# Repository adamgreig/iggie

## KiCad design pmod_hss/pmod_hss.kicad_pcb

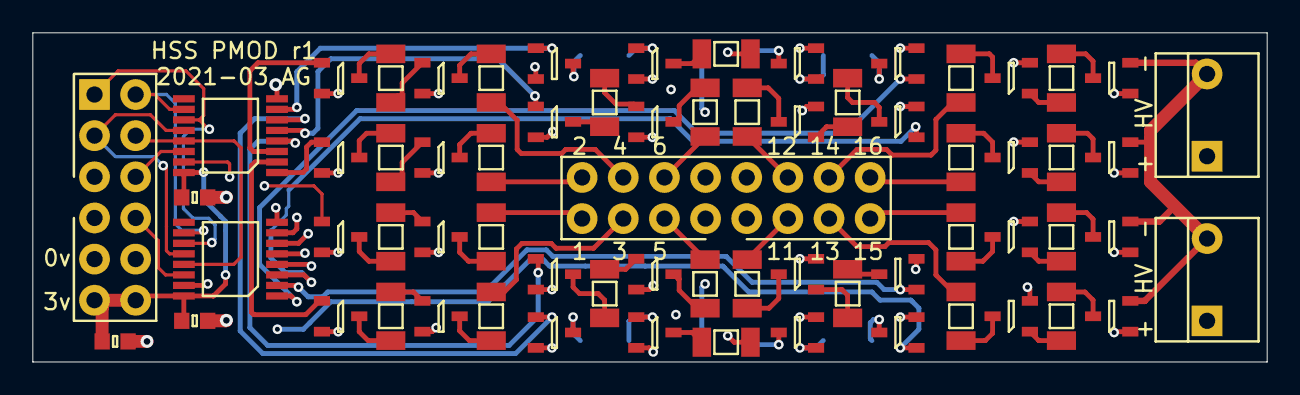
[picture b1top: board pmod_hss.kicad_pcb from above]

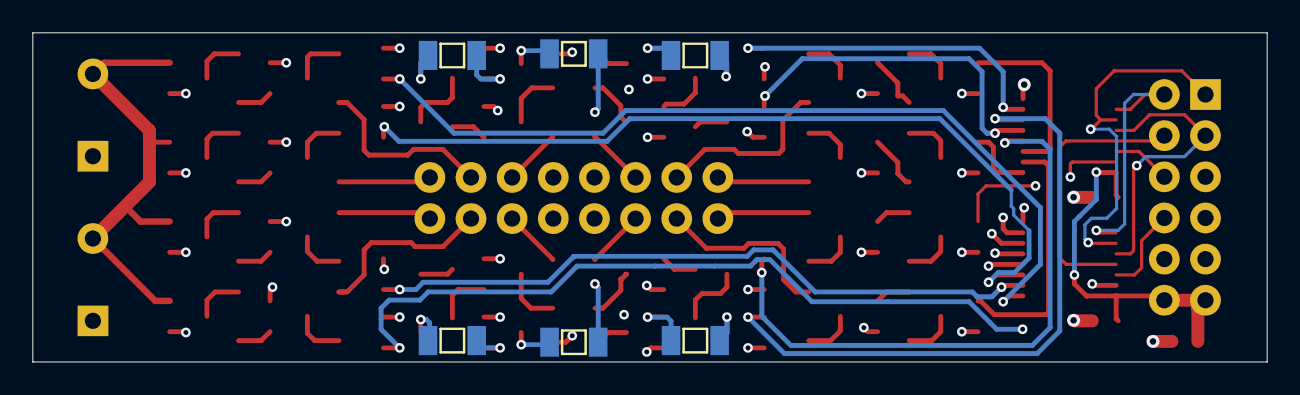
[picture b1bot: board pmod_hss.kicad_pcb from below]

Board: 4 copper layers, 76.2 x 20.3 mm, 73 parts (6 on the bottom side), 90 nets.

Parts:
C1, C2, C3: 100n; 0603
IC1, IC2: 74HC595; TSSOP-16
J1, J2: HV; MOLEX-KK-254P-03
J3: PMOD; DIL-254P-12
J4: ANODES; DIL-254P-16
Q1, Q3, Q5, Q7, Q9, Q11, Q13, Q15, Q17, Q19, Q21, Q23, Q25, Q27, Q29, Q31: PBHV9050T,215; SOT-23
Q2, Q4, Q6, Q8, Q10, Q12, Q14, Q16, Q18, Q20, Q22, Q24, Q26, Q28, Q30, Q32: DMN60H080DS-7; SOT-23
R1, R3, R5, R7, R9, R11, R13, R15, R17, R19, R21, R23, R25, R27, R29, R31: 1M; 1206
R2, R4, R6, R8, R10, R12, R14, R16, R18, R20, R22, R24, R26, R28, R30, R32: 93k1; 1206

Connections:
3v3: C1.2, C2.1, C3.2, IC1.16 (VCC), IC2.16 (VCC), J3.11, J3.12
/AN1: J4.1, R2.2
/AN2: J4.2, R18.2
/AN3: J4.3, R32.2
/AN4: J4.4, R16.2
/AN5: J4.5, R30.2
/AN6: J4.6, R14.2
/AN7: J4.7, R28.2
/AN8: J4.8, R12.2
/AN9: J4.9, R26.2
/AN10: J4.10, R10.2
/AN11: J4.11, R24.2
/AN12: J4.12, R8.2
/AN13: J4.13, R22.2
/AN14: J4.14, R6.2
/AN15: J4.15, R20.2
/AN16: J4.16, R4.2
/DS1: IC1.14 (DS), J3.6
/DS2: IC2.14 (DS), J3.8
/G1: IC1.15 (Q0), Q2.1 (G)
/G2: IC1.1 (Q1), Q18.1 (G)
/G3: IC1.2 (Q2), Q32.1 (G)
/G4: IC1.3 (Q3), Q16.1 (G)
/G5: IC1.4 (Q4), Q30.1 (G)
/G6: IC1.5 (Q5), Q14.1 (G)
/G7: IC1.6 (Q6), Q28.1 (G)
/G8: IC1.7 (Q7), Q12.1 (G)
/G9: IC2.15 (Q0), Q26.1 (G)
/G10: IC2.1 (Q1), Q10.1 (G)
/G11: IC2.2 (Q2), Q24.1 (G)
/G12: IC2.3 (Q3), Q8.1 (G)
/G13: IC2.4 (Q4), Q22.1 (G)
/G14: IC2.5 (Q5), Q6.1 (G)
/G15: IC2.6 (Q6), Q20.1 (G)
/G16: IC2.7 (Q7), Q4.1 (G)
/High-Side Switch 1/AR: Q1.3 (C), R2.1
/High-Side Switch 2/AR: Q17.3 (C), R18.1
/High-Side Switch 3/AR: Q31.3 (C), R32.1
/High-Side Switch 4/AR: Q15.3 (C), R16.1
/High-Side Switch 5/AR: Q29.3 (C), R30.1
/High-Side Switch 6/AR: Q13.3 (C), R14.1
/High-Side Switch 7/AR: Q27.3 (C), R28.1
/High-Side Switch 8/AR: Q11.3 (C), R12.1
/High-Side Switch 9/AR: Q25.3 (C), R26.1
/High-Side Switch 10/AR: Q9.3 (C), R10.1
/High-Side Switch 11/AR: Q23.3 (C), R24.1
/High-Side Switch 12/AR: Q7.3 (C), R8.1
/High-Side Switch 13/AR: Q21.3 (C), R22.1
/High-Side Switch 14/AR: Q5.3 (C), R6.1
/High-Side Switch 15/AR: Q19.3 (C), R20.1
/High-Side Switch 16/AR: Q3.3 (C), R4.1
/SHCP: IC1.11 (SHCP), IC2.11 (SHCP), J3.1
/STCP: IC1.12 (STCP), IC2.12 (STCP), J3.3
/~MR: IC1.10 (~MR), IC2.10 (~MR), J3.2
/~OE: IC1.13 (~OE), IC2.13 (~OE), J3.4
GND: C1.1, C2.2, C3.1, IC1.8 (GND), IC2.8 (GND), J3.9, J3.10
HV+: J1.1, J2.1, Q1.2 (E), Q3.2 (E), Q5.2 (E), Q7.2 (E), Q9.2 (E), Q11.2 (E), Q13.2 (E), Q15.2 (E), Q17.2 (E), Q19.2 (E), Q21.2 (E), Q23.2 (E), Q25.2 (E), Q27.2 (E), Q29.2 (E), Q31.2 (E)
HV-: J1.3, J2.3, Q2.2 (S), Q4.2 (S), Q6.2 (S), Q8.2 (S), Q10.2 (S), Q12.2 (S), Q14.2 (S), Q16.2 (S), Q18.2 (S), Q20.2 (S), Q22.2 (S), Q24.2 (S), Q26.2 (S), Q28.2 (S), Q30.2 (S), Q32.2 (S)
unnamed: Q1.1 (B), R1.2
unnamed: Q2.3 (D), R1.1
unnamed: Q3.1 (B), R3.2
unnamed: Q4.3 (D), R3.1
unnamed: Q5.1 (B), R5.2
unnamed: Q6.3 (D), R5.1
unnamed: Q7.1 (B), R7.2
unnamed: Q8.3 (D), R7.1
unnamed: Q9.1 (B), R9.2
unnamed: Q10.3 (D), R9.1
unnamed: Q11.1 (B), R11.2
unnamed: Q12.3 (D), R11.1
unnamed: Q13.1 (B), R13.2
unnamed: Q14.3 (D), R13.1
unnamed: Q15.1 (B), R15.2
unnamed: Q16.3 (D), R15.1
unnamed: Q17.1 (B), R17.2
unnamed: Q18.3 (D), R17.1
unnamed: Q19.1 (B), R19.2
unnamed: Q20.3 (D), R19.1
unnamed: Q21.1 (B), R21.2
unnamed: Q22.3 (D), R21.1
unnamed: Q23.1 (B), R23.2
unnamed: Q24.3 (D), R23.1
unnamed: Q25.1 (B), R25.2
unnamed: Q26.3 (D), R25.1
unnamed: Q27.1 (B), R27.2
unnamed: Q28.3 (D), R27.1
unnamed: Q29.1 (B), R29.2
unnamed: Q30.3 (D), R29.1
unnamed: Q31.1 (B), R31.2
unnamed: Q32.3 (D), R31.1

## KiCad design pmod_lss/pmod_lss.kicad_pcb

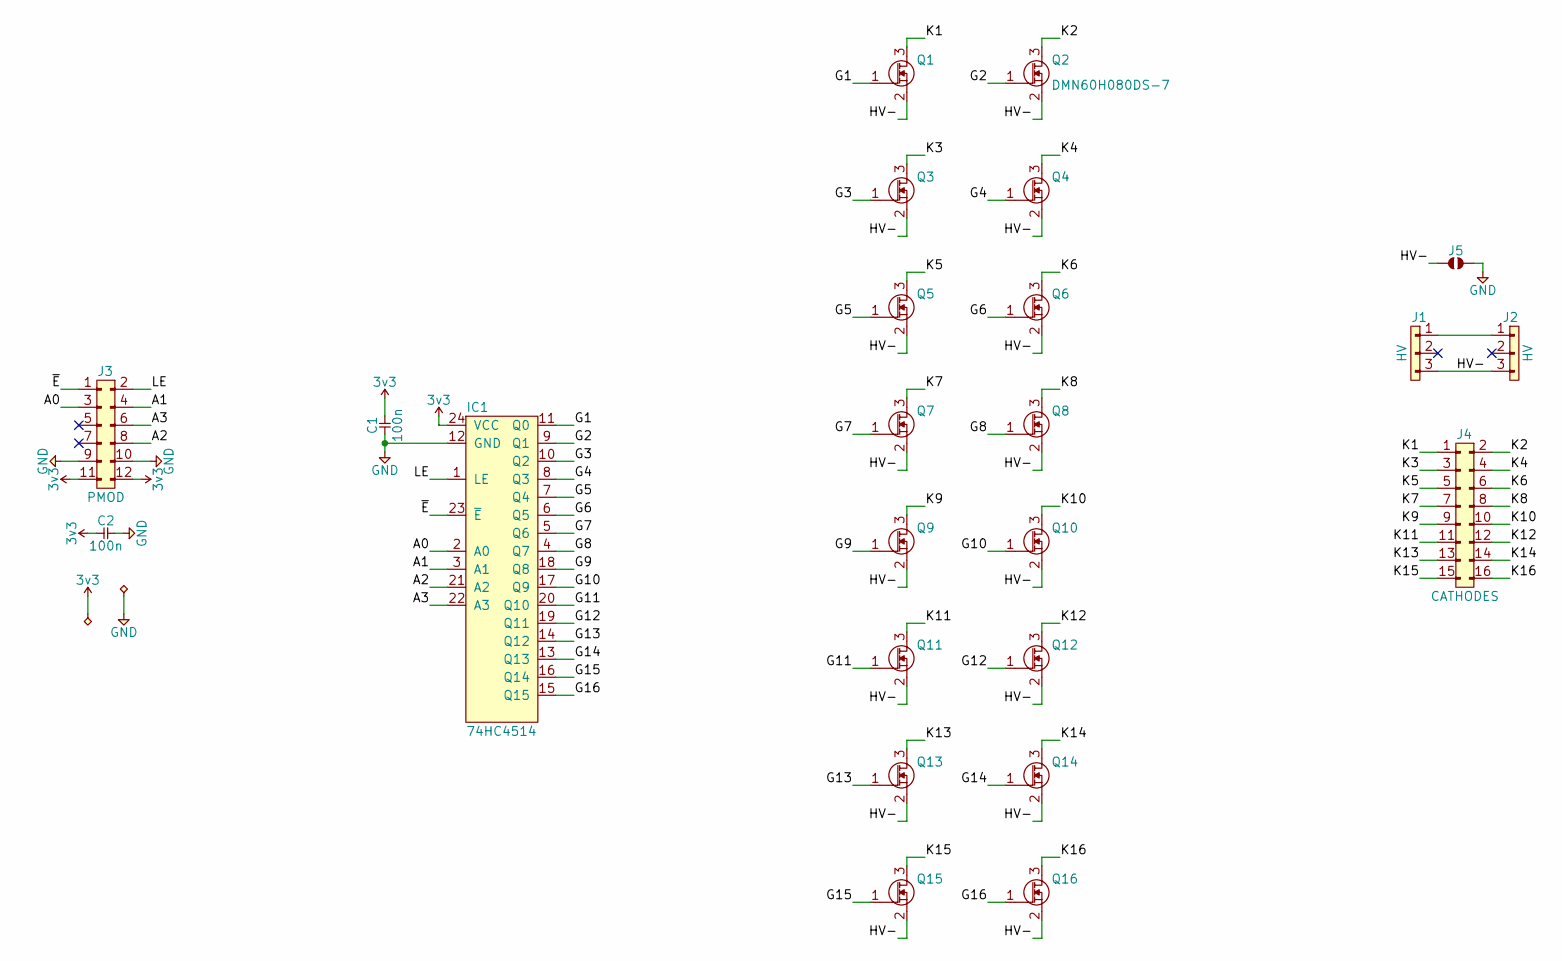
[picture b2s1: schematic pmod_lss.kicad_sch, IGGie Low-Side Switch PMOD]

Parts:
C1, C2: 100n; 0603
IC1: 74HC4514; SOIC-24-W; Farnell 2444987
J1, J2: HV; MOLEX-KK-254P-03; Farnell 1360131
J3: PMOD; DIL-254P-12; Farnell 2779668
J4: CATHODES; DIL-254P-16; Farnell 2578721
J5: SJ2
Q1, Q2, Q3, Q4, Q5, Q6, Q7, Q8, Q9, Q10, Q11, Q12, Q13, Q14, Q15, Q16: DMN60H080DS-7; SOT-23; Farnell 3127344

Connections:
3v3: C1.2, C2.1, IC1.24 (VCC), J3.11, J3.12
/A0: IC1.2 (A0), J3.3
/A1: IC1.3 (A1), J3.4
/A2: IC1.21 (A2), J3.8
/A3: IC1.22 (A3), J3.6
/G1: IC1.11 (Q0), Q1.1 (G)
/G2: IC1.9 (Q1), Q2.1 (G)
/G3: IC1.10 (Q2), Q3.1 (G)
/G4: IC1.8 (Q3), Q4.1 (G)
/G5: IC1.7 (Q4), Q5.1 (G)
/G6: IC1.6 (Q5), Q6.1 (G)
/G7: IC1.5 (Q6), Q7.1 (G)
/G8: IC1.4 (Q7), Q8.1 (G)
/G9: IC1.18 (Q8), Q9.1 (G)
/G10: IC1.17 (Q9), Q10.1 (G)
/G11: IC1.20 (Q10), Q11.1 (G)
/G12: IC1.19 (Q11), Q12.1 (G)
/G13: IC1.14 (Q12), Q13.1 (G)
/G14: IC1.13 (Q13), Q14.1 (G)
/G15: IC1.16 (Q14), Q15.1 (G)
/G16: IC1.15 (Q15), Q16.1 (G)
/HV-: J1.3, J2.3, J5.1, Q1.2 (S), Q2.2 (S), Q3.2 (S), Q4.2 (S), Q5.2 (S), Q6.2 (S), Q7.2 (S), Q8.2 (S), Q9.2 (S), Q10.2 (S), Q11.2 (S), Q12.2 (S), Q13.2 (S), Q14.2 (S), Q15.2 (S), Q16.2 (S)
/K1: J4.1, Q1.3 (D)
/K2: J4.2, Q2.3 (D)
/K3: J4.3, Q3.3 (D)
/K4: J4.4, Q4.3 (D)
/K5: J4.5, Q5.3 (D)
/K6: J4.6, Q6.3 (D)
/K7: J4.7, Q7.3 (D)
/K8: J4.8, Q8.3 (D)
/K9: J4.9, Q9.3 (D)
/K10: J4.10, Q10.3 (D)
/K11: J4.11, Q11.3 (D)
/K12: J4.12, Q12.3 (D)
/K13: J4.13, Q13.3 (D)
/K14: J4.14, Q14.3 (D)
/K15: J4.15, Q15.3 (D)
/K16: J4.16, Q16.3 (D)
/LE: IC1.1 (LE), J3.2
/~E: IC1.23 (~E), J3.1
GND: C1.1, C2.2, IC1.12 (GND), J3.9, J3.10, J5.2
unnamed: J1.1, J2.1

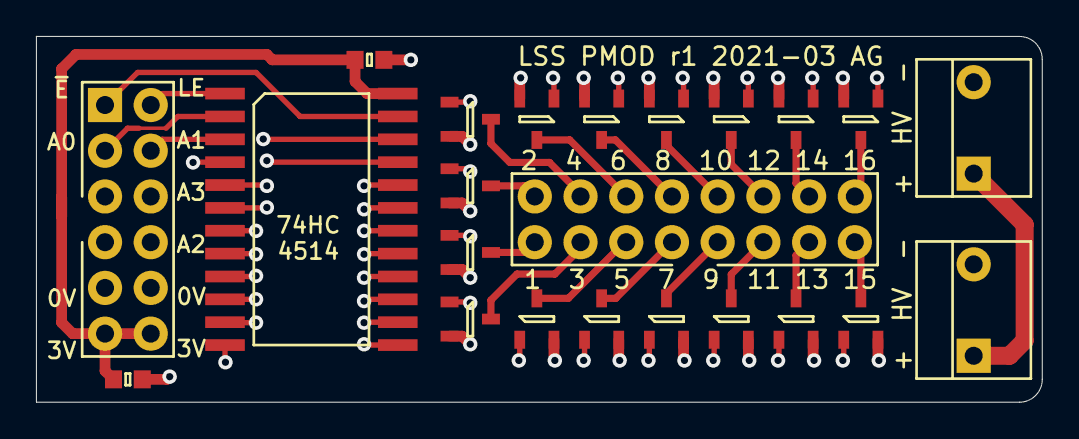
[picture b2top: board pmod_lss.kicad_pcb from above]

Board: 4 copper layers, 55.9 x 20.3 mm, 24 parts (1 on the bottom side), 42 nets.

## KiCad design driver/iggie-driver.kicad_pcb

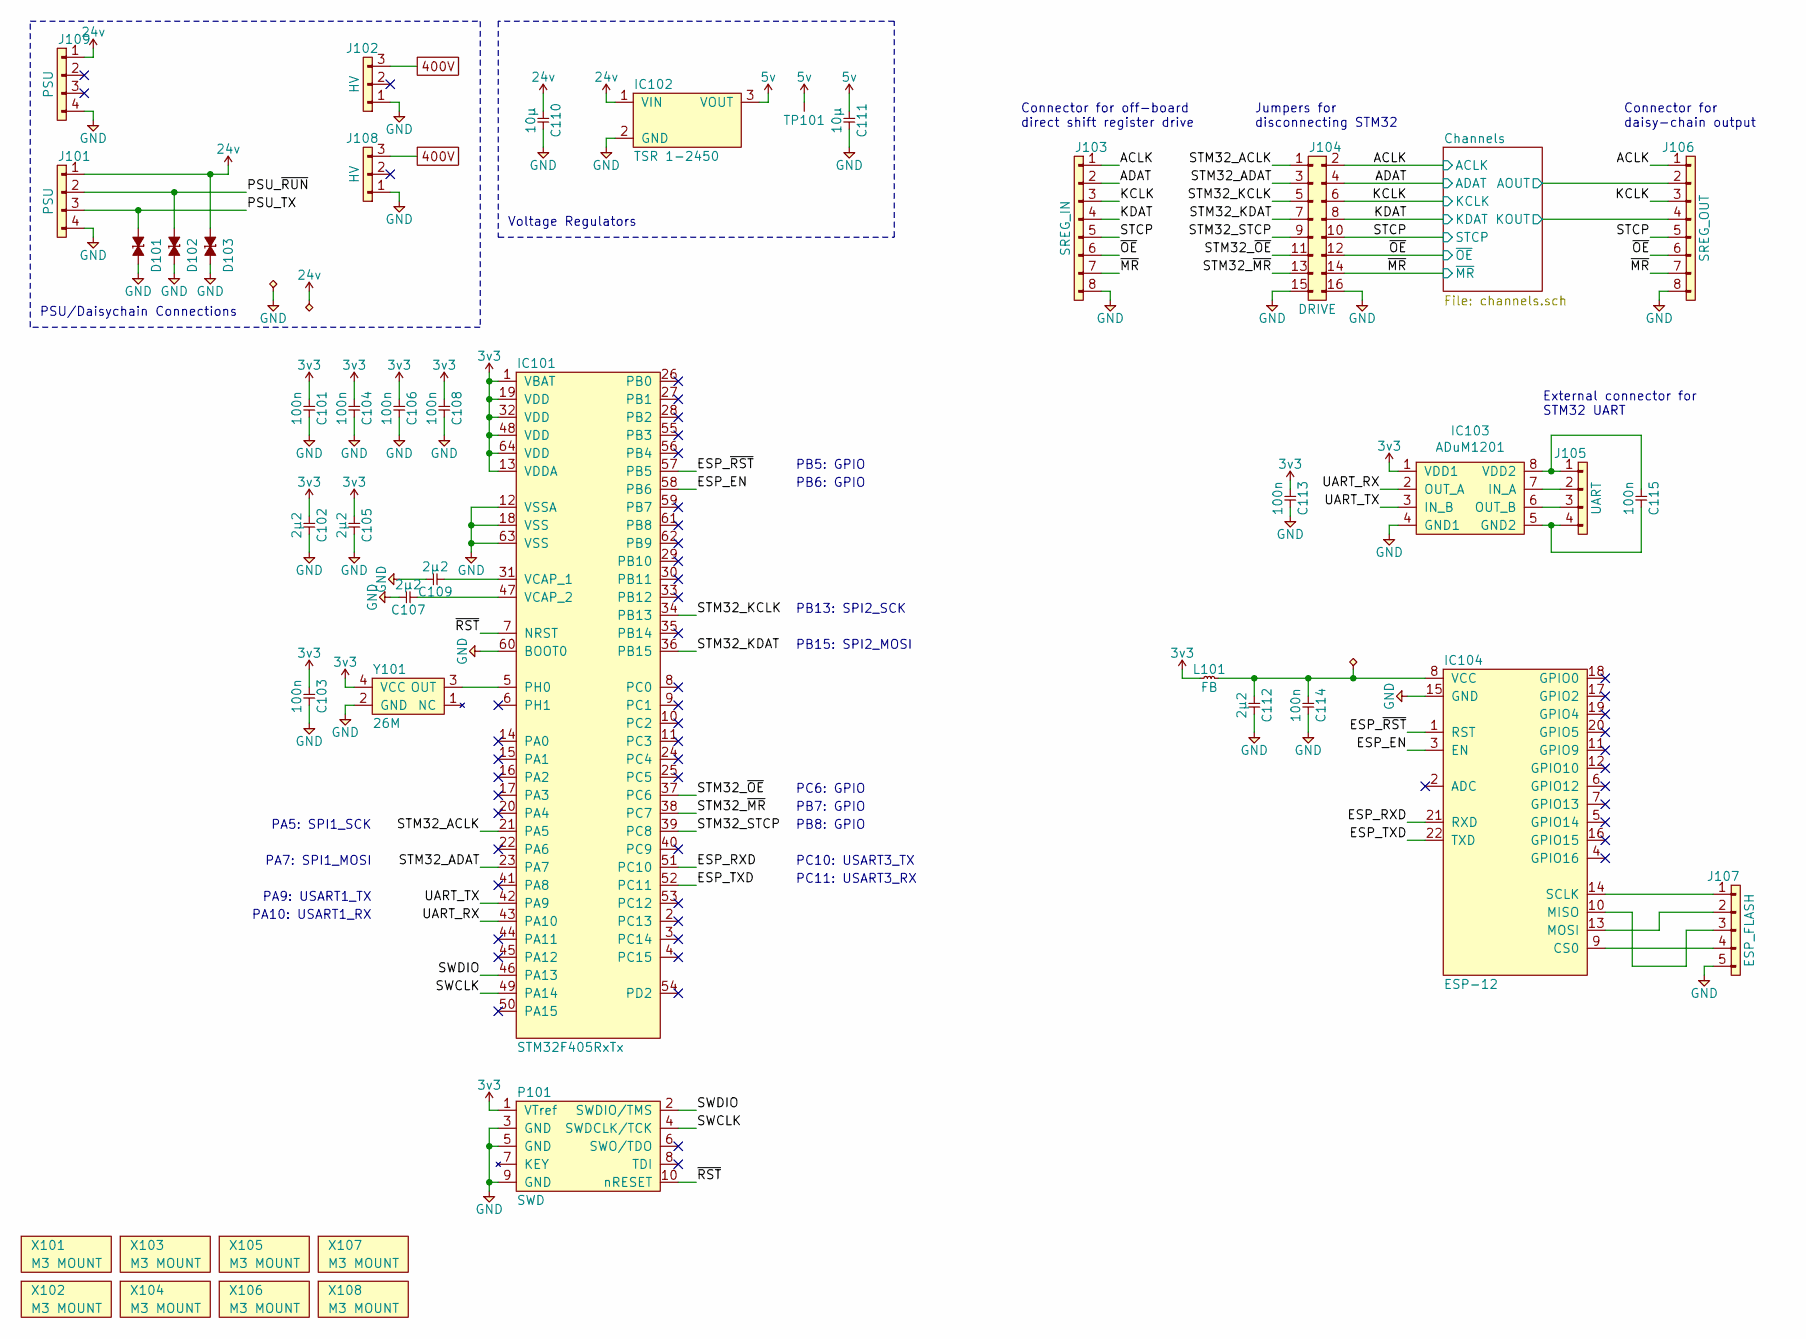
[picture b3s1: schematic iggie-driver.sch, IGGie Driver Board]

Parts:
C101, C103, C104, C106, C108, C113, C114, C115: 100n; 0603; Voltage 50V; Farnell 2320803
C102, C105, C107, C109, C112: 2µ2; 0603; Farnell 2346896
C110, C111: 10µ; 1210; Voltage 50V; Farnell 2781426
D101, D102, D103: ESD_DIODE; 0603; Voltage 24V; Farnell 2368174
IC101: STM32F405RxTx; LQFP-64; Farnell 2064363
IC102: TSR 1-2450; TSR1; Farnell 1696320
IC103: ADuM1201; SOIC-8; Farnell 1078202
IC104: ESP-12
J101, J109: PSU; MOLEX-KK-254P-04; Farnell 1360132
J102, J108: HV; MOLEX-KK-254P-03; Farnell 1360131
J103: SREG_IN; MOLEX-PICOBLADE-53398-0871; Farnell 1125371
J104: DRIVE; DIL-254P-16; Farnell 1593445
J105: UART; MOLEX-PICOBLADE-53398-0471; Farnell 1125367
J106: SREG_OUT; MOLEX-PICOBLADE-53398-0871; Farnell 1125371
J107: ESP_FLASH; SIL-254P-05
L101: FB; 0603; Farnell 1515747
P101: SWD; FTSH-105-01-F-D-K; Farnell 2856437
TP101: TESTPAD
X101, X102, X103, X104, X105, X106, X107, X108: M3 MOUNT; M3_MOUNT
Y101: 26M; XTAL-25x20; Farnell 2986171

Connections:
3v3: C101.1, C102.1, C103.1, C104.1, C105.1, C106.1, C108.1, C113.1, IC101.1 (VBAT), IC101.13 (VDDA), IC101.19 (VDD), IC101.32 (VDD), IC101.48 (VDD), IC101.64 (VDD), IC103.1 (VDD1), L101.1, P101.1 (VTref), Y101.4 (VCC); also elsewhere on the board
5v: C111.1, IC102.3 (VOUT), TP101.1
24v: C110.1, D103.1, IC102.1 (VIN), J101.1, J109.1
400V: J102.3, J108.3; also elsewhere on the board
/ACLK: J103.1, J104.2, J106.1; also elsewhere on the board
/ADAT: J103.2, J104.4; also elsewhere on the board
/Channels/AOUT: J106.2; also elsewhere on the board
/Channels/KOUT: J106.4; also elsewhere on the board
/ESP_EN: IC101.58 (PB6), IC104.3 (EN)
/ESP_RXD: IC101.51 (PC10), IC104.21 (RXD)
/ESP_TXD: IC101.52 (PC11), IC104.22 (TXD)
/ESP_~RST: IC101.57 (PB5), IC104.1 (RST)
/KCLK: J103.3, J104.6, J106.3; also elsewhere on the board
/KDAT: J103.4, J104.8; also elsewhere on the board
/PSU_TX: D101.1, J101.3
/PSU_~RUN: D102.1, J101.2
/STCP: J103.5, J104.10, J106.5; also elsewhere on the board
/STM32_ACLK: IC101.21 (PA5), J104.1
/STM32_ADAT: IC101.23 (PA7), J104.3
/STM32_KCLK: IC101.34 (PB13), J104.5
/STM32_KDAT: IC101.36 (PB15), J104.7
/STM32_STCP: IC101.39 (PC8), J104.9
/STM32_~MR: IC101.38 (PC7), J104.13
/STM32_~OE: IC101.37 (PC6), J104.11
/SWCLK: IC101.49 (PA14), P101.4 (SWDCLK/TCK)
/SWDIO: IC101.46 (PA13), P101.2 (SWDIO/TMS)
/UART_RX: IC101.43 (PA10), IC103.2 (OUT_A)
/UART_TX: IC101.42 (PA9), IC103.3 (IN_B)
/~MR: J103.7, J104.14, J106.7; also elsewhere on the board
/~OE: J103.6, J104.12, J106.6; also elsewhere on the board
/~RST: IC101.7 (NRST), P101.10 (nRESET)
GND: C101.2, C102.2, C103.2, C104.2, C105.2, C106.2, C107.2, C108.2, C109.2, C110.2, C111.2, C112.2, C113.2, C114.2, D101.2, D102.2, D103.2, IC101.12 (VSSA), IC101.18 (VSS), IC101.60 (BOOT0), IC101.63 (VSS), IC102.2 (GND), IC103.4 (GND1), IC104.15 (GND), J101.4, J102.1, J103.8, J104.15, J104.16, J106.8, J107.5, J108.1, J109.4, P101.3 (GND), P101.5 (GND), P101.9 (GND), Y101.2 (GND); also elsewhere on the board
unnamed: C107.1, IC101.47 (VCAP_2)
unnamed: C109.1, IC101.31 (VCAP_1)
unnamed: C112.1, C114.1, IC104.8 (VCC), L101.2
unnamed: C115.1, IC103.8 (VDD2), J105.1
unnamed: C115.2, IC103.5 (GND2), J105.4
unnamed: IC101.5 (PH0), Y101.3 (OUT)
unnamed: IC103.6 (OUT_B), J105.3
unnamed: IC103.7 (IN_A), J105.2
unnamed: IC104.9 (CS0), J107.4
unnamed: IC104.10 (MISO), J107.3
unnamed: IC104.13 (MOSI), J107.2
unnamed: IC104.14 (SCLK), J107.1

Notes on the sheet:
PSU/Daisychain Connections
Voltage Regulators
Jumpers for disconnecting STM32
Connector for off-board direct shift register drive
External connector for STM32 UART
PA5: SPI1_SCK
PA7: SPI1_MOSI
PB13: SPI2_SCK
PB15: SPI2_MOSI
PA9: USART1_TX
PA10: USART1_RX
PC10: USART3_TX
PC11: USART3_RX
PB5: GPIO
PB6: GPIO
PC6: GPIO
PB7: GPIO
PB8: GPIO
Connector for daisy-chain output

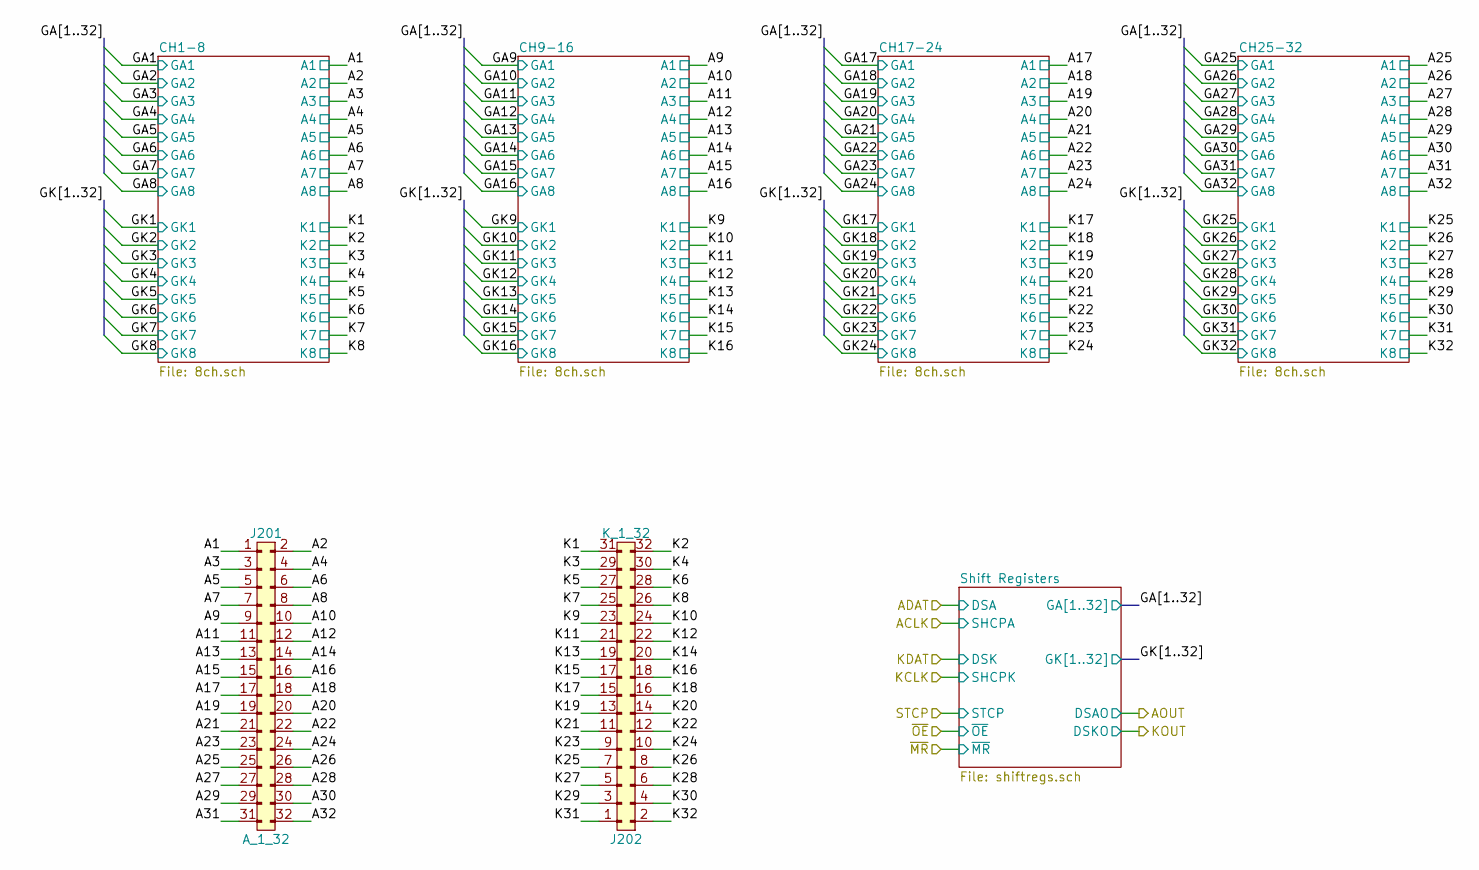
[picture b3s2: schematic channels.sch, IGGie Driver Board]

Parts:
J201: A_1_32; DIL-254P-32; MPN IPL1-116-01-L-D-RA-K; Farnell 2856270
J202: K_1_32; DIL-254P-32; MPN IPL1-116-01-L-D-RA-K; Farnell 2856270

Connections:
/Channels/A1: J201.1; also elsewhere on the board
/Channels/A2: J201.2; also elsewhere on the board
/Channels/A3: J201.3; also elsewhere on the board
/Channels/A4: J201.4; also elsewhere on the board
/Channels/A5: J201.5; also elsewhere on the board
/Channels/A6: J201.6; also elsewhere on the board
/Channels/A7: J201.7; also elsewhere on the board
/Channels/A8: J201.8; also elsewhere on the board
/Channels/A9: J201.9; also elsewhere on the board
/Channels/A10: J201.10; also elsewhere on the board
/Channels/A11: J201.11; also elsewhere on the board
/Channels/A12: J201.12; also elsewhere on the board
/Channels/A13: J201.13; also elsewhere on the board
/Channels/A14: J201.14; also elsewhere on the board
/Channels/A15: J201.15; also elsewhere on the board
/Channels/A16: J201.16; also elsewhere on the board
/Channels/A17: J201.17; also elsewhere on the board
/Channels/A18: J201.18; also elsewhere on the board
/Channels/A19: J201.19; also elsewhere on the board
/Channels/A20: J201.20; also elsewhere on the board
/Channels/A21: J201.21; also elsewhere on the board
/Channels/A22: J201.22; also elsewhere on the board
/Channels/A23: J201.23; also elsewhere on the board
/Channels/A24: J201.24; also elsewhere on the board
/Channels/A25: J201.25; also elsewhere on the board
/Channels/A26: J201.26; also elsewhere on the board
/Channels/A27: J201.27; also elsewhere on the board
/Channels/A28: J201.28; also elsewhere on the board
/Channels/A29: J201.29; also elsewhere on the board
/Channels/A30: J201.30; also elsewhere on the board
/Channels/A31: J201.31; also elsewhere on the board
/Channels/A32: J201.32; also elsewhere on the board
/Channels/K1: J202.31; also elsewhere on the board
/Channels/K2: J202.32; also elsewhere on the board
/Channels/K3: J202.29; also elsewhere on the board
/Channels/K4: J202.30; also elsewhere on the board
/Channels/K5: J202.27; also elsewhere on the board
/Channels/K6: J202.28; also elsewhere on the board
/Channels/K7: J202.25; also elsewhere on the board
/Channels/K8: J202.26; also elsewhere on the board
/Channels/K9: J202.23; also elsewhere on the board
/Channels/K10: J202.24; also elsewhere on the board
/Channels/K11: J202.21; also elsewhere on the board
/Channels/K12: J202.22; also elsewhere on the board
/Channels/K13: J202.19; also elsewhere on the board
/Channels/K14: J202.20; also elsewhere on the board
/Channels/K15: J202.17; also elsewhere on the board
/Channels/K16: J202.18; also elsewhere on the board
/Channels/K17: J202.15; also elsewhere on the board
/Channels/K18: J202.16; also elsewhere on the board
/Channels/K19: J202.13; also elsewhere on the board
/Channels/K20: J202.14; also elsewhere on the board
/Channels/K21: J202.11; also elsewhere on the board
/Channels/K22: J202.12; also elsewhere on the board
/Channels/K23: J202.9; also elsewhere on the board
/Channels/K24: J202.10; also elsewhere on the board
/Channels/K25: J202.7; also elsewhere on the board
/Channels/K26: J202.8; also elsewhere on the board
/Channels/K27: J202.5; also elsewhere on the board
/Channels/K28: J202.6; also elsewhere on the board
/Channels/K29: J202.3; also elsewhere on the board
/Channels/K30: J202.4; also elsewhere on the board
/Channels/K31: J202.1; also elsewhere on the board
/Channels/K32: J202.2; also elsewhere on the board
